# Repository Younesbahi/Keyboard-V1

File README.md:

# Mechanical Keyboard V1

## What this is
This is a custom mechanical keyboard that I designed from scratch. I designed the PCB, selected all the components, and created the case in Fusion 360.

The keyboard uses a Raspberry Pi Pico microcontroller, a diode matrix, and a custom layout. It also has a 0.96-inch OLED screen.

## Features
- Custom keyboard layout
- Number row acts as function keys when Fn is held
- Mechanical MX-style switches
- Diode matrix
-  OLED screen
- 3D-printed case

## Layout

## Bill of Materials (BOM)

| Item                | Description                        | Quantity | Unit Price | Total Price | URL                                                                                                                                                                                                                  | Running Total ($ with Tax) | Total w/ Shipping |
|--------------------|------------------------------------|---------|------------|------------|----------------------------------------------------------------------------------------------------------------------------------------------------------------------------------------------------------------------|---------------------------|-----------------|
| PCB                | Keyboard PCB                       | 5       | $3.46      | $17.30     | [JLCPCB](https://jlcpcb.com/)                                                                                                                                                                                       | $30.31                    | $33.65          |
| MCU                | Raspberry Pi Pico                  | 1       | $2.64      | $2.64      | [AliExpress](https://www.aliexpress.com/item/1005006615944063.html?spm=a2g0o.cart.0.0.34ff38dak8zI5C&mp=1&pdp_npi=6%40dis%21USD%21USD%202.64%21USD%202.64%21%21USD%202.64%21%21%21%402101e8f317680786548757992efb8a%2112000037830228611%21ct%21CA%216994311444%21%211%210%21) | $2.64                     | $2.64           |
| Switches           | Outemu Cream Yellow                | 70      | $0.267     | $18.69     | [AliExpress](https://www.aliexpress.com/item/1005006263528658.html?spm=a2g0o.cart.0.0.3ea738daCRAVLy&mp=1&pdp_npi=6%40dis%21USD%21USD%2018.69%21USD%2018.69%21%21USD%2018.69%21%21%21%4021033d1217680085731295916ed11c%2112000036520553929%21ct%21CA%216994311444%21%211%210%21) | $18.69                    | $18.69          |
| Diodes             | 1N4148 DO-35 IN4148                | 100     | $0.0202    | $2.02      | [AliExpress](https://www.aliexpress.com/item/1005007807649334.html?spm=a2g0o.cart.0.0.3ea738daCRAVLy&mp=1&pdp_npi=6%40dis%21USD%21USD%202.02%21USD%202.02%21%21USD%202.02%21%21%21%4021033d1217680085731295916ed11c%2112000042270438468%21ct%21CA%216994311444%21%211%210%21) | $2.02                     | $2.02           |
| Stabilizers        | PCB-mount stabilizers              | 1       | $6.86      | $6.86      | [AliExpress](https://www.aliexpress.com/item/1005004229140548.html?spm=a2g0o.detail.0.0.42705OPY5OPYZb&mp=1&pdp_npi=6%40dis%21USD%21USD%206.86%21USD%206.86%21%21USD%206.86%21%21%21%402103122117680092977833580ea6cf%2112000028456713257%21ct%21CA%216994311444%21%211%210%21) | $6.86                     | $6.86           |
| Standoff            | M3 Standoffs 6mm                   | 50      | $0.0386    | $1.93      | [AliExpress](https://www.aliexpress.com/item/32539100523.html?spm=a2g0o.detail.0.0.3c99DXfpDXfpkB&mp=1&pdp_npi=6%40dis%21USD%21USD%201.61%21USD%201.61%21%21USD%201.61%21%21%21%402103122117680093888736500ea6cf%2112000036690751384%21ct%21CA%216994311444%21%211%210%21&pdp_ext_f=%7B%22cart2PdpParams%22%3A%7B%22pdpBusinessMode%22%3A%22retail%22%7D%7D) | $1.93                     | $1.93           |
| Screws              | M3 Screws 5mm                      | 50      | $0.0322    | $1.61      | [AliExpress](https://www.aliexpress.com/item/32539100523.html?spm=a2g0o.productlist.0.0.df4a6416YomQSb&mp=1&pdp_npi=6%40dis%21USD%21USD%201.61%21USD%201.61%21%21USD%201.61%21%21%21%402103122117680095346584016ea6cf%2112000036690751384%21ct%21CA%216994311444%21%211%210%21&pdp_ext_f=%7B%22cart2PdpParams%22%3A%7B%22pdpBusinessMode%22%3A%22retail%22%7D%7D) | $1.61                     | $1.61           |
| Inserts             | M3 Heat inserts                    | 50      | $0.0452    | $2.26      | [AliExpress](https://www.aliexpress.com/item/1005003582355741.html?spm=a2g0o.detail.0.0.6235j6Sfj6SfOC&mp=1&pdp_npi=6%40dis%21USD%21USD%202.26%21USD%202.26%21%21USD%202.26%21%21%21%402103122117680095514434382ea6cf%2112000026370649726%21ct%21CA%216994311444%21%211%210%21) | $2.26                     | $2.26           |
| KeyCaps             | Keycaps for Cherry MX Switches     | 1       | $11.49     | $11.49     | [AliExpress](https://www.aliexpress.com/item/1005009580866548.html?spm=a2g0o.cart.0.0.5b8538daREDYj3&mp=1&pdp_npi=6%40dis%21USD%21USD%2011.49%21USD%2011.49%21%21USD%2011.49%21%21%21%402103122117680097581772043ea6cf%2112000049526083200%21ct%21CA%216994311444%21%211%210%21) | $11.49                    | $11.49          |
| Case                | 3D Printed case                     | 1       | -          | -          | -                                                                                                                                                                                                                    | -                         | -               |
| I2C OLED 0.91"      | OLED screen                        | 1       | $2.53      | $2.53      | [AliExpress](https://www.aliexpress.com/item/1005006297182727.html?spm=a2g0o.cart.0.0.34ff38dak8zI5C&mp=1&pdp_npi=6%40dis%21USD%21USD%202.53%21USD%202.53%21%21USD%202.53%21%21%21%402101e8f317680786548757992efb8a%2112000036657700927%21ct%21CA%216994311444%21%211%210%21) | $2.53                     | $2.53           |

**Total Cost:** $83.68  (Not including Case)
| Schematic | PCB Layout | PCB render |
|--------------|--------------|--------------|
| |  ||

## Render

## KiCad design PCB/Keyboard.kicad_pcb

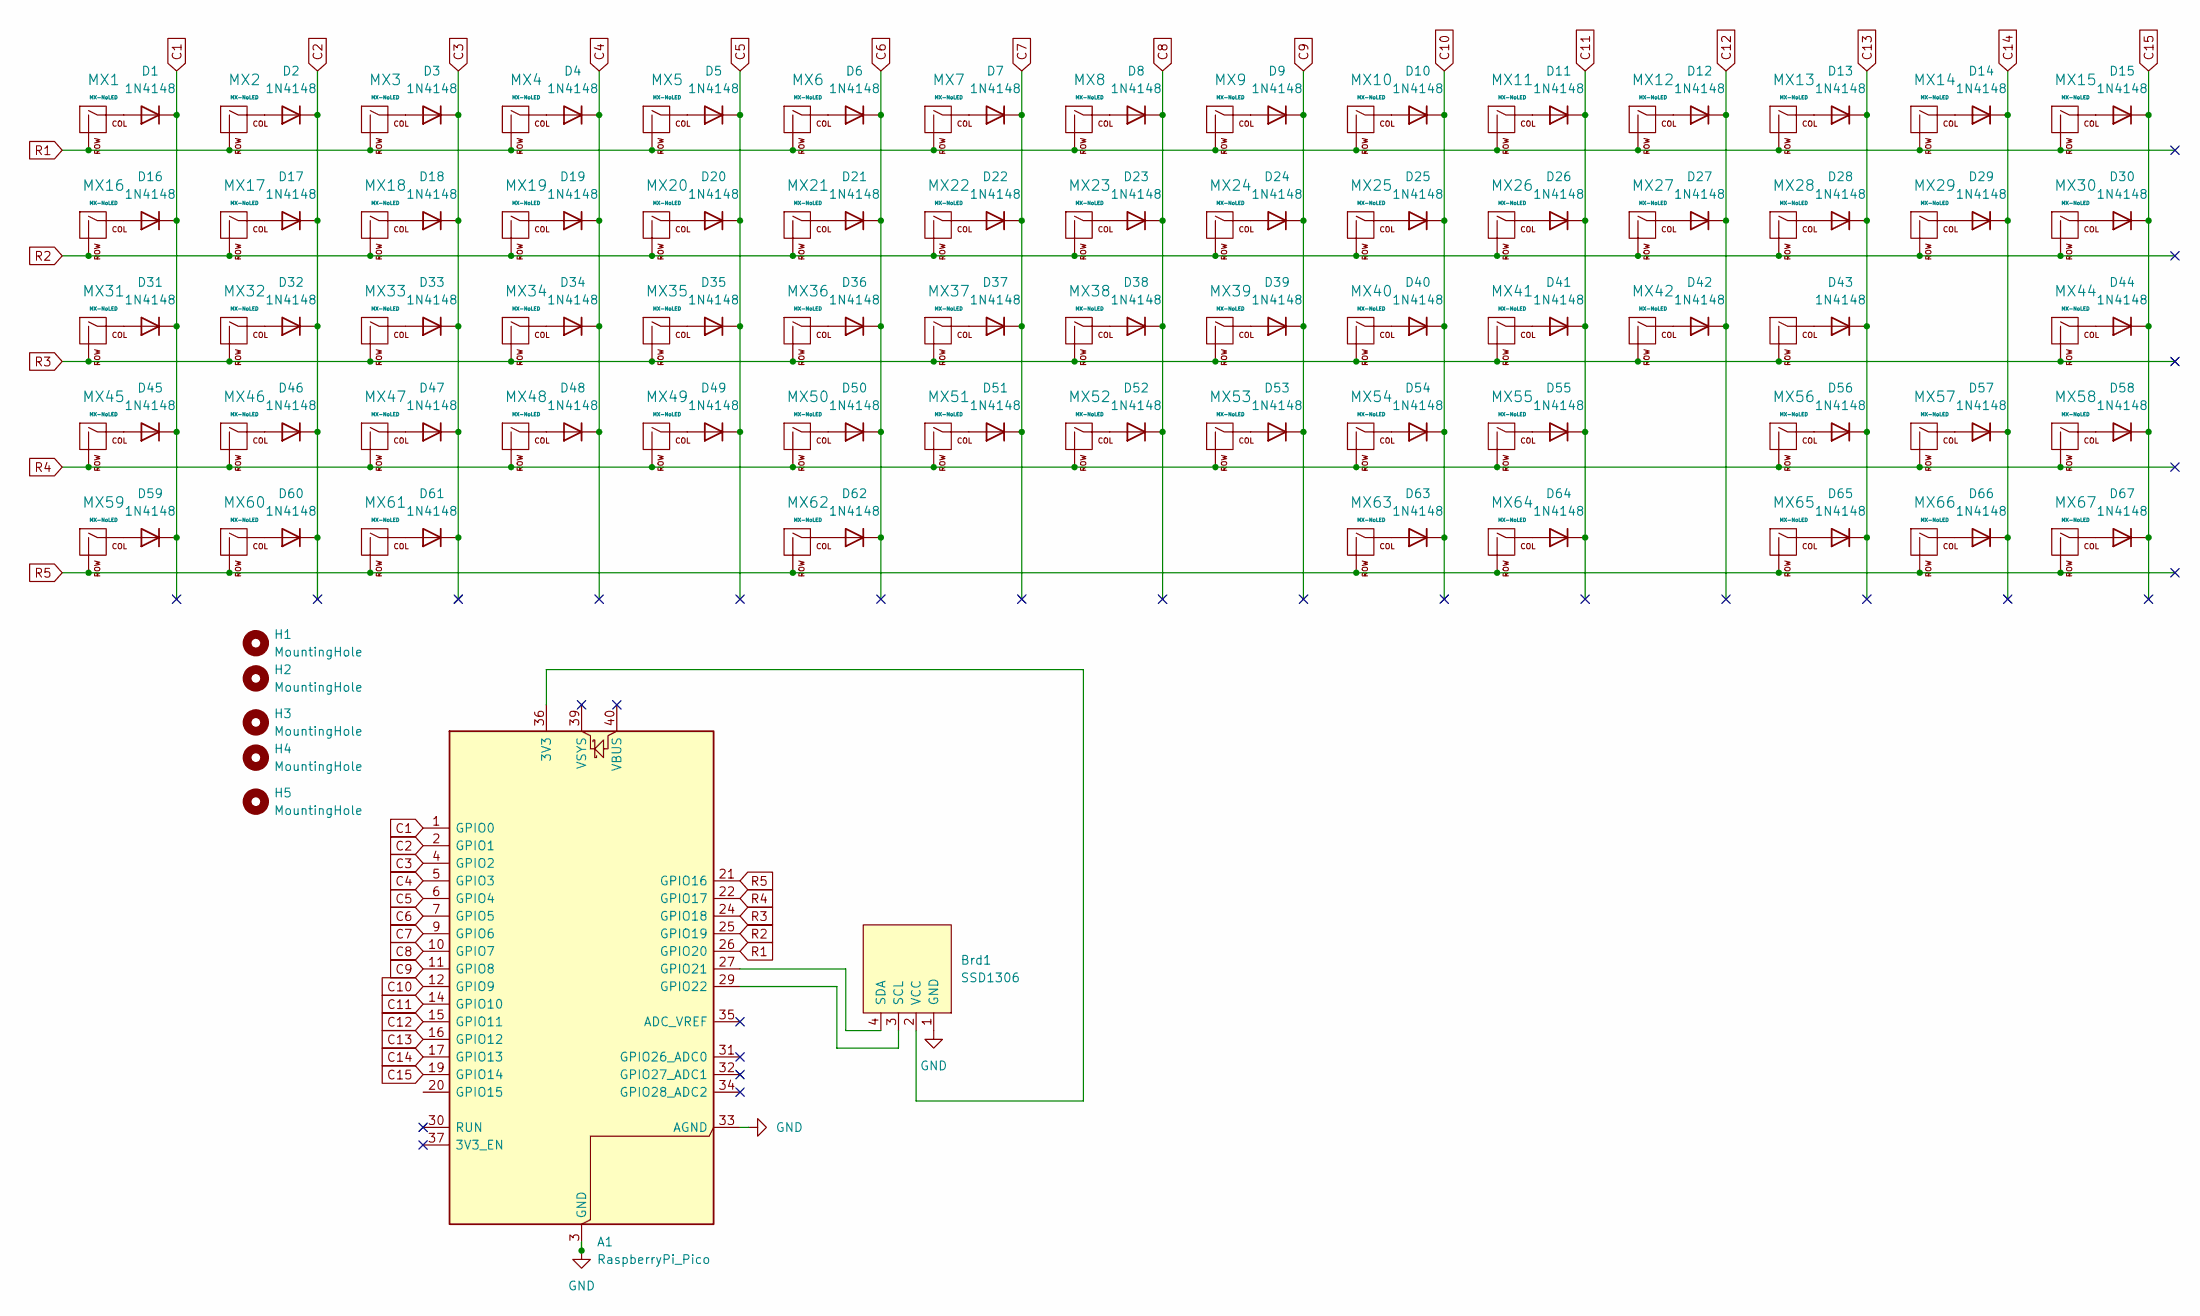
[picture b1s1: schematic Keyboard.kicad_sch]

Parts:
A1: RaspberryPi_Pico; RaspberryPi_Pico_Common
Brd1: SSD1306; 128x64OLED
D1, D2, D3, D4, D5, D6, D7, D8, D9, D10, D11, D12, D13, D14, D15, D16, D17, D18, D19, D20, D21, D22, D23, D24, D25, D26, D27, D28, D29, D30, D31, D32, D33, D34, D35, D36, D37, D38, D39, D40, D41, D42, D43, D44, D45, D46, D47, D48, D49, D50, D51, D52, D53, D54, D55, D56, D57, D58, D59, D60, D61, D62, D63, D64, D65, D66, D67: 1N4148; D_DO-35_SOD27_P7.62mm_Horizontal
H1, H2, H3, H4, H5: MountingHole; MountingHole_3.2mm_M3
MX1, MX2, MX3, MX4, MX5, MX6, MX7, MX8, MX9, MX10, MX11, MX12, MX13, MX15, MX17, MX18, MX19, MX20, MX21, MX22, MX23, MX24, MX25, MX26, MX27, MX28, MX30, MX32, MX33, MX34, MX35, MX36, MX37, MX38, MX39, MX40, MX41, MX42, MX44, MX46, MX47, MX48, MX49, MX50, MX51, MX52, MX53, MX54, MX55, MX58, MX67: MX-NoLED; MXOnly-1U-NoLED
MX14: MX-NoLED; MXOnly-2U
MX16, MX29, MX56: MX-NoLED; MXOnly-1.5U-NoLED
MX31: MX-NoLED; MXOnly-1.75U-NoLED
MX43, MX45: MX-NoLED; MXOnly-2.25U-NoLED
MX57, MX59, MX60, MX61, MX63, MX64, MX65, MX66: MX-NoLED; MXOnly-1.25U-NoLED
MX62: MX-NoLED; MXOnly-6.25U-NoLED

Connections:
C1: A1.1 (GPIO0), D1.1 (K), D16.1 (K), D31.1 (K), D45.1 (K), D59.1 (K)
C2: A1.2 (GPIO1), D2.1 (K), D17.1 (K), D32.1 (K), D46.1 (K), D60.1 (K)
C3: A1.4 (GPIO2), D3.1 (K), D18.1 (K), D33.1 (K), D47.1 (K), D61.1 (K)
C4: A1.5 (GPIO3), D4.1 (K), D19.1 (K), D34.1 (K), D48.1 (K)
C5: A1.6 (GPIO4), D5.1 (K), D20.1 (K), D35.1 (K), D49.1 (K)
C6: A1.7 (GPIO5), D6.1 (K), D21.1 (K), D36.1 (K), D50.1 (K), D62.1 (K)
C7: A1.9 (GPIO6), D7.1 (K), D22.1 (K), D37.1 (K), D51.1 (K)
C8: A1.10 (GPIO7), D8.1 (K), D23.1 (K), D38.1 (K), D52.1 (K)
C9: A1.11 (GPIO8), D9.1 (K), D24.1 (K), D39.1 (K), D53.1 (K)
C10: A1.12 (GPIO9), D10.1 (K), D25.1 (K), D40.1 (K), D54.1 (K), D63.1 (K)
C11: A1.14 (GPIO10), D11.1 (K), D26.1 (K), D41.1 (K), D55.1 (K), D64.1 (K)
C12: A1.15 (GPIO11), D12.1 (K), D27.1 (K), D42.1 (K)
C13: A1.16 (GPIO12), D13.1 (K), D28.1 (K), D43.1 (K), D56.1 (K), D65.1 (K)
C14: A1.17 (GPIO13), D14.1 (K), D29.1 (K), D57.1 (K), D66.1 (K)
C15: A1.19 (GPIO14), D15.1 (K), D30.1 (K), D44.1 (K), D58.1 (K), D67.1 (K)
GND: A1.3 (GND), A1.8 (GND), A1.13 (GND), A1.18 (GND), A1.23 (GND), A1.28 (GND), A1.33 (AGND), A1.38 (GND), Brd1.1 (GND)
unnamed: A1.36 (3V3), Brd1.2 (VCC)
unnamed: A1.27 (GPIO21), Brd1.4 (SDA)
unnamed: A1.29 (GPIO22), Brd1.3 (SCL)
unnamed: D1.2 (A), MX1.1 (COL)
unnamed: D2.2 (A), MX2.1 (COL)
unnamed: D3.2 (A), MX3.1 (COL)
unnamed: D4.2 (A), MX4.1 (COL)
unnamed: D5.2 (A), MX5.1 (COL)
unnamed: D6.2 (A), MX6.1 (COL)
unnamed: D7.2 (A), MX7.1 (COL)
unnamed: D8.2 (A), MX8.1 (COL)
unnamed: D9.2 (A), MX9.1 (COL)
unnamed: D10.2 (A), MX10.1 (COL)
unnamed: D11.2 (A), MX11.1 (COL)
unnamed: D12.2 (A), MX12.1 (COL)
unnamed: D13.2 (A), MX13.1 (COL)
unnamed: D14.2 (A), MX14.1 (COL)
unnamed: D15.2 (A), MX15.1 (COL)
unnamed: D16.2 (A), MX16.1 (COL)
unnamed: D17.2 (A), MX17.1 (COL)
unnamed: D18.2 (A), MX18.1 (COL)
unnamed: D19.2 (A), MX19.1 (COL)
unnamed: D20.2 (A), MX20.1 (COL)
unnamed: D21.2 (A), MX21.1 (COL)
unnamed: D22.2 (A), MX22.1 (COL)
unnamed: D23.2 (A), MX23.1 (COL)
unnamed: D24.2 (A), MX24.1 (COL)
unnamed: D25.2 (A), MX25.1 (COL)
unnamed: D26.2 (A), MX26.1 (COL)
unnamed: D27.2 (A), MX27.1 (COL)
unnamed: D28.2 (A), MX28.1 (COL)
unnamed: D29.2 (A), MX29.1 (COL)
unnamed: D30.2 (A), MX30.1 (COL)
unnamed: D31.2 (A), MX31.1 (COL)
unnamed: D32.2 (A), MX32.1 (COL)
unnamed: D33.2 (A), MX33.1 (COL)
unnamed: D34.2 (A), MX34.1 (COL)
unnamed: D35.2 (A), MX35.1 (COL)
unnamed: D36.2 (A), MX36.1 (COL)
unnamed: D37.2 (A), MX37.1 (COL)
unnamed: D38.2 (A), MX38.1 (COL)
unnamed: D39.2 (A), MX39.1 (COL)
unnamed: D40.2 (A), MX40.1 (COL)
unnamed: D41.2 (A), MX41.1 (COL)
unnamed: D42.2 (A), MX42.1 (COL)
unnamed: D43.2 (A), MX43.1 (COL)
unnamed: D44.2 (A), MX44.1 (COL)
unnamed: D45.2 (A), MX45.1 (COL)
unnamed: D46.2 (A), MX46.1 (COL)
unnamed: D47.2 (A), MX47.1 (COL)
unnamed: D48.2 (A), MX48.1 (COL)
unnamed: D49.2 (A), MX49.1 (COL)
unnamed: D50.2 (A), MX50.1 (COL)
unnamed: D51.2 (A), MX51.1 (COL)
unnamed: D52.2 (A), MX52.1 (COL)
unnamed: D53.2 (A), MX53.1 (COL)
unnamed: D54.2 (A), MX54.1 (COL)
unnamed: D55.2 (A), MX55.1 (COL)
unnamed: D56.2 (A), MX56.1 (COL)
unnamed: D57.2 (A), MX57.1 (COL)
unnamed: D58.2 (A), MX58.1 (COL)
unnamed: D59.2 (A), MX59.1 (COL)
unnamed: D60.2 (A), MX60.1 (COL)
unnamed: D61.2 (A), MX61.1 (COL)
unnamed: D62.2 (A), MX62.1 (COL)
unnamed: D63.2 (A), MX63.1 (COL)
unnamed: D64.2 (A), MX64.1 (COL)
unnamed: D65.2 (A), MX65.1 (COL)
unnamed: D66.2 (A), MX66.1 (COL)
unnamed: D67.2 (A), MX67.1 (COL)
R1: A1.26 (GPIO20), MX1.2 (ROW), MX2.2 (ROW), MX3.2 (ROW), MX4.2 (ROW), MX5.2 (ROW), MX6.2 (ROW), MX7.2 (ROW), MX8.2 (ROW), MX9.2 (ROW), MX10.2 (ROW), MX11.2 (ROW), MX12.2 (ROW), MX13.2 (ROW), MX14.2 (ROW), MX15.2 (ROW)
R2: A1.25 (GPIO19), MX16.2 (ROW), MX17.2 (ROW), MX18.2 (ROW), MX19.2 (ROW), MX20.2 (ROW), MX21.2 (ROW), MX22.2 (ROW), MX23.2 (ROW), MX24.2 (ROW), MX25.2 (ROW), MX26.2 (ROW), MX27.2 (ROW), MX28.2 (ROW), MX29.2 (ROW), MX30.2 (ROW)
R3: A1.24 (GPIO18), MX31.2 (ROW), MX32.2 (ROW), MX33.2 (ROW), MX34.2 (ROW), MX35.2 (ROW), MX36.2 (ROW), MX37.2 (ROW), MX38.2 (ROW), MX39.2 (ROW), MX40.2 (ROW), MX41.2 (ROW), MX42.2 (ROW), MX43.2 (ROW), MX44.2 (ROW)
R4: A1.22 (GPIO17), MX45.2 (ROW), MX46.2 (ROW), MX47.2 (ROW), MX48.2 (ROW), MX49.2 (ROW), MX50.2 (ROW), MX51.2 (ROW), MX52.2 (ROW), MX53.2 (ROW), MX54.2 (ROW), MX55.2 (ROW), MX56.2 (ROW), MX57.2 (ROW), MX58.2 (ROW)
R5: A1.21 (GPIO16), MX59.2 (ROW), MX60.2 (ROW), MX61.2 (ROW), MX62.2 (ROW), MX63.2 (ROW), MX64.2 (ROW), MX65.2 (ROW), MX66.2 (ROW), MX67.2 (ROW)

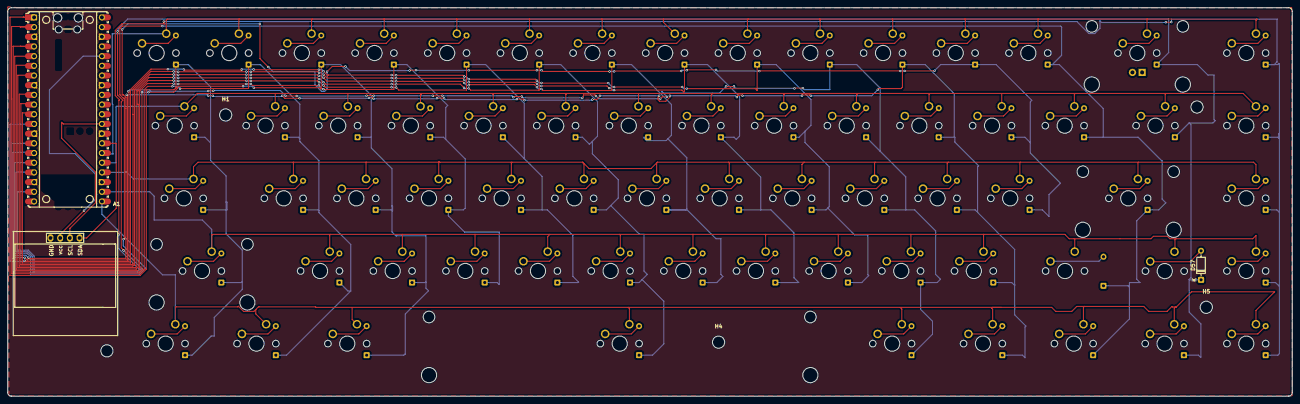
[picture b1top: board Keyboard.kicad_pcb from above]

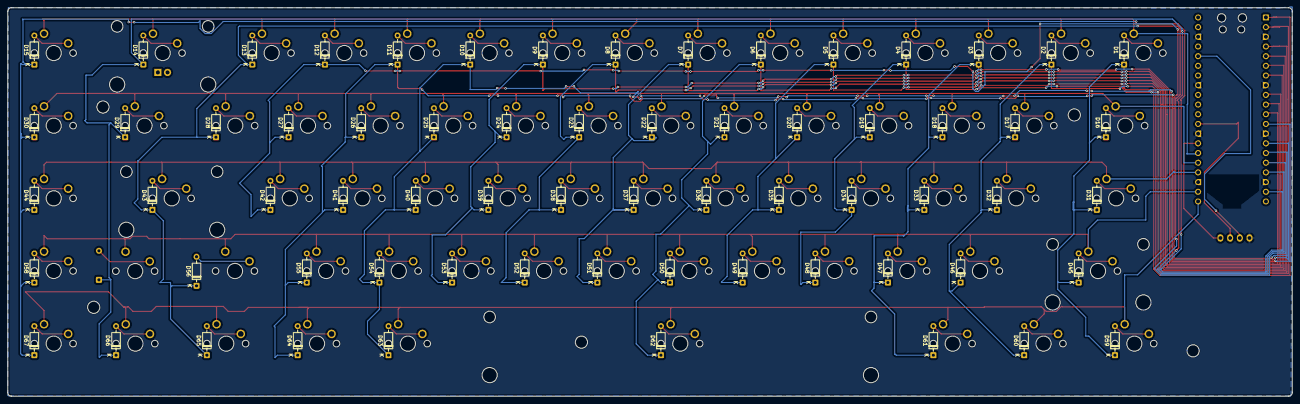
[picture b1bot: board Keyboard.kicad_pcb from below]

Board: 2 copper layers, 336.8 x 101.9 mm, 141 parts (66 on the bottom side), 91 nets.

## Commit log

2026-01-09 Create Temp
2026-01-11 Added PCB Files
